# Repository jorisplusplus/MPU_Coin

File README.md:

# Campzone 2019 Coin
The Campzone coin used to collect the campzone 2019 badge

https://wiki.badge.team/CZ19

Soldering video here https://www.youtube.com/watch?v=MPRI4y40bMs

To refill zone:
1. change arc degree to 360
2. refill
3. change arc degree back to 330

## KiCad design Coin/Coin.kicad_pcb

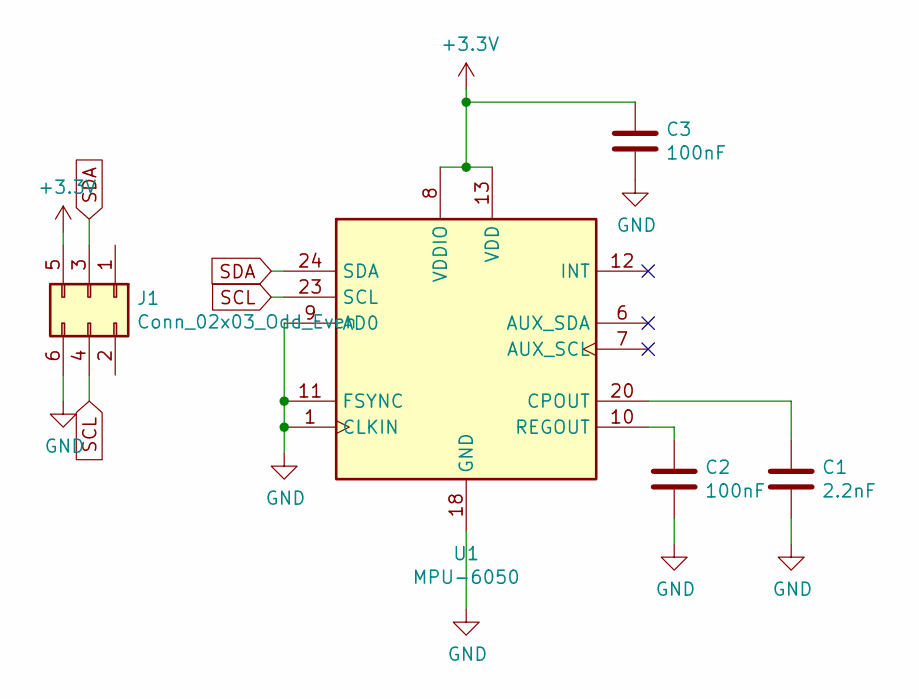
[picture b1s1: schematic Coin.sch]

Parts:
C1: 2.2nF; C_0805_2012Metric_Pad1.15x1.40mm_HandSolder
C2, C3: 100nF; C_0805_2012Metric_Pad1.15x1.40mm_HandSolder
J1: Conn_02x03_Odd_Even; PinSocket_2x03_P2.54mm_Vertical
U1: MPU-6050; QFN-24-1EP_4x4mm_P0.5mm_EP2.7x2.6mm

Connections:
+3V3: C3.1, J1.5, U1.8 (VDDIO), U1.13 (VDD)
GND: C1.2, C2.2, C3.2, J1.6, U1.1 (CLKIN), U1.9 (AD0), U1.11 (FSYNC), U1.18 (GND)
unnamed: C1.1, U1.20 (CPOUT)
unnamed: C2.1, U1.10 (REGOUT)
SCL: J1.4, U1.23 (SCL)
SDA: J1.3, U1.24 (SDA)

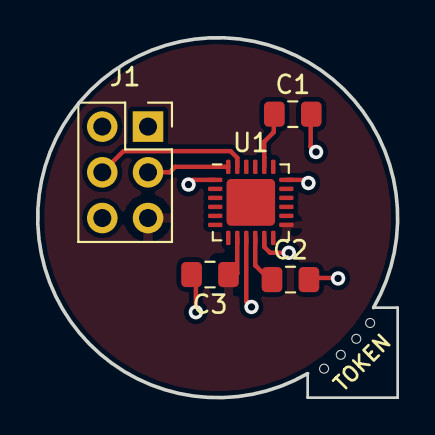
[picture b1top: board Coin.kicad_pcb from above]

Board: 2 copper layers, 20.0 x 20.0 mm, 5 parts (0 on the bottom side), 6 nets.

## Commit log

2019-06-24 Updated silkscreen
2019-06-24 Update capacitor value
2019-08-07 updated Schematic
